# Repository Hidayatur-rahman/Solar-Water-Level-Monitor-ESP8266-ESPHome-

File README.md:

# Solar Water Level Monitor (ESP8266 + ESPHome)

A solar-powered water tank level monitoring system built around the ESP8266 (ESP-12E), designed in KiCad and running on ESPHome. It measures water level with an ultrasonic sensor, monitors battery current/voltage, and charges itself from a solar panel with a selectable-voltage MPPT charger.

## Features

- **Water level sensing** using an HC-SR04 ultrasonic distance sensor
- **Solar MPPT charging** via CN3791, with jumper-selectable input voltage (6V / 9V / 12V)
- **Battery current & voltage monitoring** using an INA219 sensor
- **1S Li-ion protection** (over-charge / over-discharge / over-current) using DW01A + FS8205A
- **5V boost converter** (MT3608) to power the ESP8266 and sensors from a single Li-ion cell
- **Deep sleep support** for low power consumption between readings
- **ESPHome integration** — no custom firmware needed, works directly with Home Assistant

## Hardware Overview

| Block | Component | Notes |
|---|---|---|
| MCU | ESP-12E (ESP8266) | Runs ESPHome |
| Water sensor | HC-SR04 | 5V supply, echo signal stepped down to 3.3V via voltage divider |
| Current/voltage sensor | INA219 | I2C, monitors battery current (charge & discharge) |
| Boost converter | MT3608 | Steps battery voltage (3.0–4.2V) up to 5V |
| Solar charger | CN3791 | MPPT buck charger, up to 4A, input jumper-selectable for 6V/9V/12V panels |
| Battery protection | DW01A + FS8205A | Standard 1S Li-ion protection circuit |
| Battery | 1x 18650 Li-ion | Not included on the board |

## Pin Connections (ESP-12E)

| Function | GPIO |
|---|---|
| I2C SDA (INA219) | GPIO4 |
| I2C SCL (INA219) | GPIO5 |
| HC-SR04 Trig | GPIO14 |
| HC-SR04 Echo (via divider) | GPIO12 |
| Deep sleep wake | GPIO16 → RST (via solder jumper) |

## Solar Panel Voltage Selection

The CN3791 MPPT tracking voltage is set by closing one solder jumper on the board.
| Panel    | Target MPPT | R18  |         |       VMPPT |
| -------- | ----------: | ---: | ------: | ----------: |
| **6 V**  |      ~5,0 V | 200k | **68k** |  **4,75 V** |
| **9 V**  |      ~8,0 V | 200k | **39k** |  **7,38 V** |
| **12 V** |     ~10,2 V | 200k | **33k** |  **8,50 V** |

> Only close **one** jumper at a time.

## Getting Started

1. Flash the board with [ESPHome](https://esphome.io/), using the provided YAML configuration (`esphome/water-level-sensor.yaml`)
2. Connect the HC-SR04, battery, and solar panel
3. Set the solar jumper according to your panel's voltage
4. Add the device to Home Assistant via the ESPHome integration

## PCB

- Designed in KiCad, 2-layer, 60x60mm
- Gerber files and schematic are in the `/hardware` folder

## License

MIT — feel free to use, modify, and build upon this project.

## Disclaimer

This is a hobbyist/DIY project. Double-check battery polarity and solar jumper settings before powering on. No warranty is provided — build and use at your own risk.

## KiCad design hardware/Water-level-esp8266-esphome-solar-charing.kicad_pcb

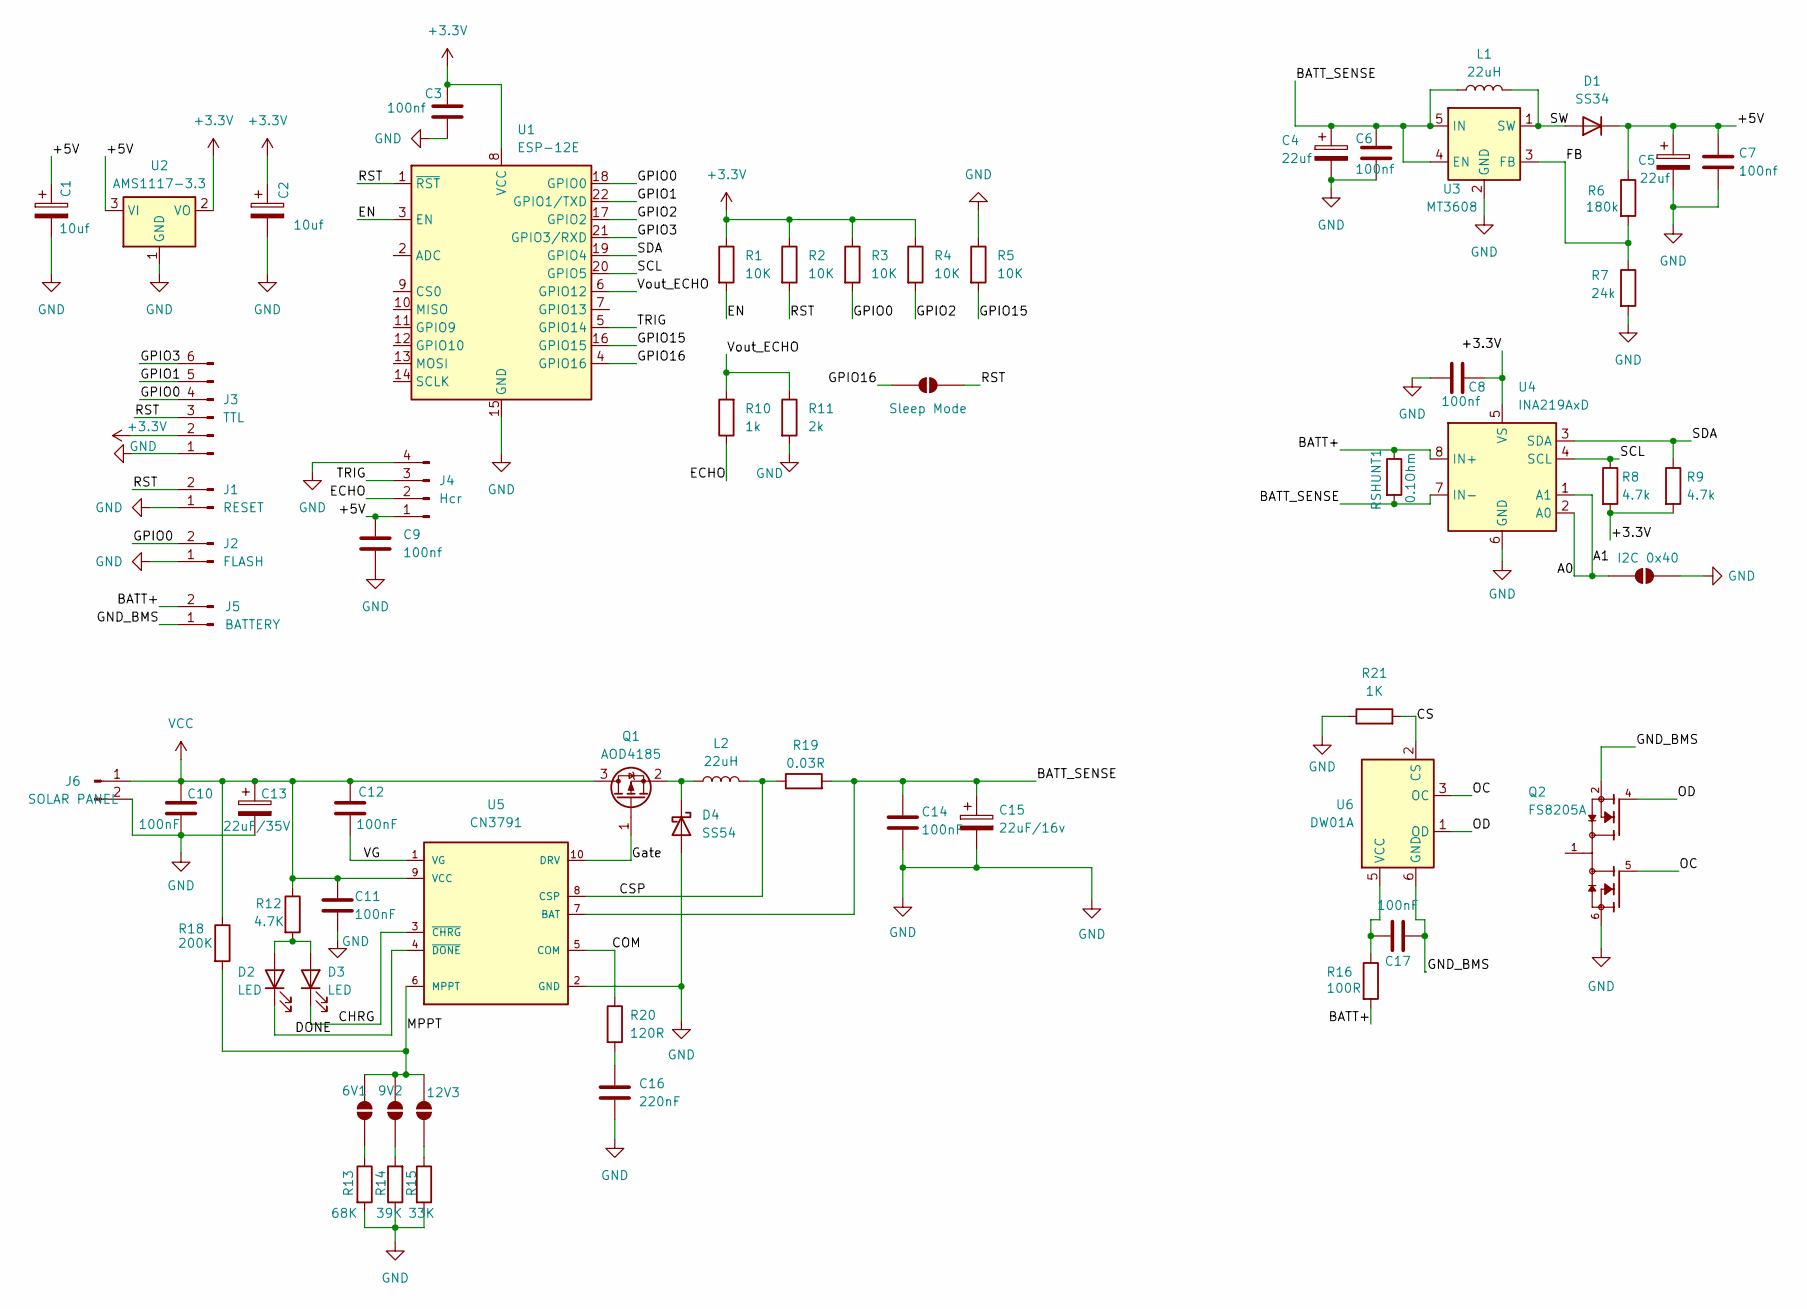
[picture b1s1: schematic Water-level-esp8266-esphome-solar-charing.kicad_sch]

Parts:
6V1, 9V2, 12V3: SolderJumper_2_Open; SolderJumper-2_P1.3mm_Open_RoundedPad1.0x1.5mm
C1, C2: 10uf; C_1206_3216Metric_Pad1.33x1.80mm_HandSolder
C3, C6, C7, C8, C9: 100nf; C_0603_1608Metric_Pad1.08x0.95mm_HandSolder
C4, C5: 22uf; C_1206_3216Metric_Pad1.33x1.80mm_HandSolder
C10, C11, C12, C14, C17: 100nF; C_0603_1608Metric_Pad1.08x0.95mm_HandSolder
C13: 22uF/35V; CP_Elec_8x6.9
C15: 22uF/16v; CP_Elec_8x6.9
C16: 220nF; C_0603_1608Metric_Pad1.08x0.95mm_HandSolder
D1: SS34; D_1206_3216Metric_Pad1.42x1.75mm_HandSolder
D2, D3: LED; LED_0805_2012Metric_Pad1.15x1.40mm_HandSolder
D4: SS54; D_SMA
J1: RESET; PinHeader_1x02_P2.54mm_Vertical
J2: FLASH; PinHeader_1x02_P2.54mm_Vertical
J3: TTL; PinHeader_1x06_P2.54mm_Vertical
J4: Hcr; PinHeader_1x04_P2.54mm_Vertical
J5: BATTERY; JST_PH_B2B-PH-K_1x02_P2.00mm_Vertical
J6: SOLAR PANEL; JST_PH_B2B-PH-K_1x02_P2.00mm_Vertical
JP1: Sleep Mode; SolderJumper-2_P1.3mm_Open_Pad1.0x1.5mm
JP2: I2C 0x40; SolderJumper-2_P1.3mm_Open_Pad1.0x1.5mm
L1: 22uH; L_Changjiang_FNR4030S
L2: 22uH; L_Changjiang_FXL1030
Q1: AOD4185; TO-252-2
Q2: FS8205A; SOP65P640X120-8N; PARTREV 1.7
R1, R2, R3, R4, R5: 10K; R_0805_2012Metric_Pad1.20x1.40mm_HandSolder
R6: 180k; R_0805_2012Metric_Pad1.20x1.40mm_HandSolder
R7: 24k; R_0805_2012Metric_Pad1.20x1.40mm_HandSolder
R8, R9: 4.7k; R_0805_2012Metric_Pad1.20x1.40mm_HandSolder
R10: 1k; R_0805_2012Metric_Pad1.20x1.40mm_HandSolder
R11: 2k; R_0805_2012Metric_Pad1.20x1.40mm_HandSolder
R12: 4.7K; R_0805_2012Metric_Pad1.20x1.40mm_HandSolder
R13: 68K; R_0805_2012Metric_Pad1.20x1.40mm_HandSolder
R14: 39K; R_0805_2012Metric_Pad1.20x1.40mm_HandSolder
R15: 33K; R_0805_2012Metric_Pad1.20x1.40mm_HandSolder
R16: 100R; R_0805_2012Metric_Pad1.20x1.40mm_HandSolder
R18: 200K; R_0805_2012Metric_Pad1.20x1.40mm_HandSolder
R19: 0.03R; R_2512_6332Metric_Pad1.40x3.35mm_HandSolder
R20: 120R; R_0805_2012Metric_Pad1.20x1.40mm_HandSolder
R21: 1K; R_0805_2012Metric_Pad1.20x1.40mm_HandSolder
RSHUNT1: 0.1Ohm; R_2512_6332Metric_Pad1.40x3.35mm_HandSolder
U1: ESP-12E
U2: AMS1117-3.3; SOT-223-3_TabPin2
U3: MT3608; SOT-23-6
U4: INA219AxD; SOIC-8_3.9x4.9mm_P1.27mm
U5: CN3791; CN3791_SSOP10
U6: DW01A; SOT-23-6

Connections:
+3.3V: C2.1, C3.1, C8.2, J3.2, R1.1, R2.1, R3.1, R4.1, R8.2, R9.2, U1.8 (VCC), U2.2 (VO), U4.5 (VS)
/+5V: C1.1, C5.1, C7.1, C9.1, D1.1 (K), J4.1, R6.1, U2.3 (VI)
/A0: JP2.2 (B), U4.1 (A1), U4.2 (A0)
/BATT+: J5.2, R16.2, RSHUNT1.1, U4.8 (IN+)
/BATT_SENSE: C4.1, C6.1, C14.1, C15.1, L1.1, R19.2, RSHUNT1.2, U3.4 (EN), U3.5 (IN), U4.7 (IN-), U5.7 (BAT)
/CHRG: D3.1 (K), U5.3 (~CHRG)
/COM: R20.1, U5.5 (COM)
/CS: R21.2, U6.2 (CS)
/CSP: L2.2, R19.1, U5.8 (CSP)
/DONE: D2.1 (K), U5.4 (~DONE)
/ECHO: J4.2, R10.1
/EN: R1.2, U1.3 (EN)
/FB: R6.2, R7.1, U3.3 (FB)
/GND_BMS: C17.2, J5.1, Q2.2, Q2.3, U6.6 (GND)
/GPIO0: J2.2, J3.4, R3.2, U1.18 (GPIO0)
/GPIO1: J3.5, U1.22 (GPIO1/TXD)
/GPIO2: R4.2, U1.17 (GPIO2)
/GPIO3: J3.6, U1.21 (GPIO3/RXD)
/GPIO15: R5.2, U1.16 (GPIO15)
/GPIO16: JP1.2 (B), U1.4 (GPIO16)
/Gate: Q1.1 (G), U5.10 (DRV)
/MPPT: 6V1.2 (B), 9V2.1 (A), 12V3.2 (B), R18.2, U5.6 (MPPT)
/OC: Q2.5, U6.3 (OC)
/OD: Q2.4, U6.1 (OD)
/RST: J1.2, J3.3, JP1.1 (A), R2.2, U1.1 (~RST)
/SCL: R8.1, U1.20 (GPIO5), U4.4 (SCL)
/SDA: R9.1, U1.19 (GPIO4), U4.3 (SDA)
/SW: D1.2 (A), L1.2, U3.1 (SW)
/TRIG: J4.3, U1.5 (GPIO14)
/VG: C12.2, U5.1 (VG)
/Vout_ECHO: R10.2, R11.1, U1.6 (GPIO12)
GND: C1.2, C2.2, C3.2, C4.2, C5.2, C6.2, C7.2, C8.1, C9.2, C10.2, C11.2, C13.2, C14.2, C15.2, C16.2, D4.2 (A), J1.1, J2.1, J3.1, J4.4, J6.2, JP2.1 (A), Q2.6, Q2.7, R5.1, R7.2, R11.2, R13.2, R14.1, R15.2, R21.1, U1.15 (GND), U2.1 (GND), U3.2 (GND), U4.6 (GND), U5.2 (GND)
unnamed: 6V1.1 (A), R13.1
unnamed: 9V2.2 (B), R14.2
unnamed: 12V3.1 (A), R15.1
unnamed: C16.1, R20.2
unnamed: D2.2 (A), D3.2 (A), R12.2
unnamed: D4.1 (K), L2.1, Q1.2 (S)
unnamed: Q2.1, Q2.8
unnamed: C17.1, R16.1, U6.5 (VCC)
VCC: C10.1, C11.1, C12.1, C13.1, J6.1, Q1.3 (D), R12.1, R18.1, U5.9 (VCC)

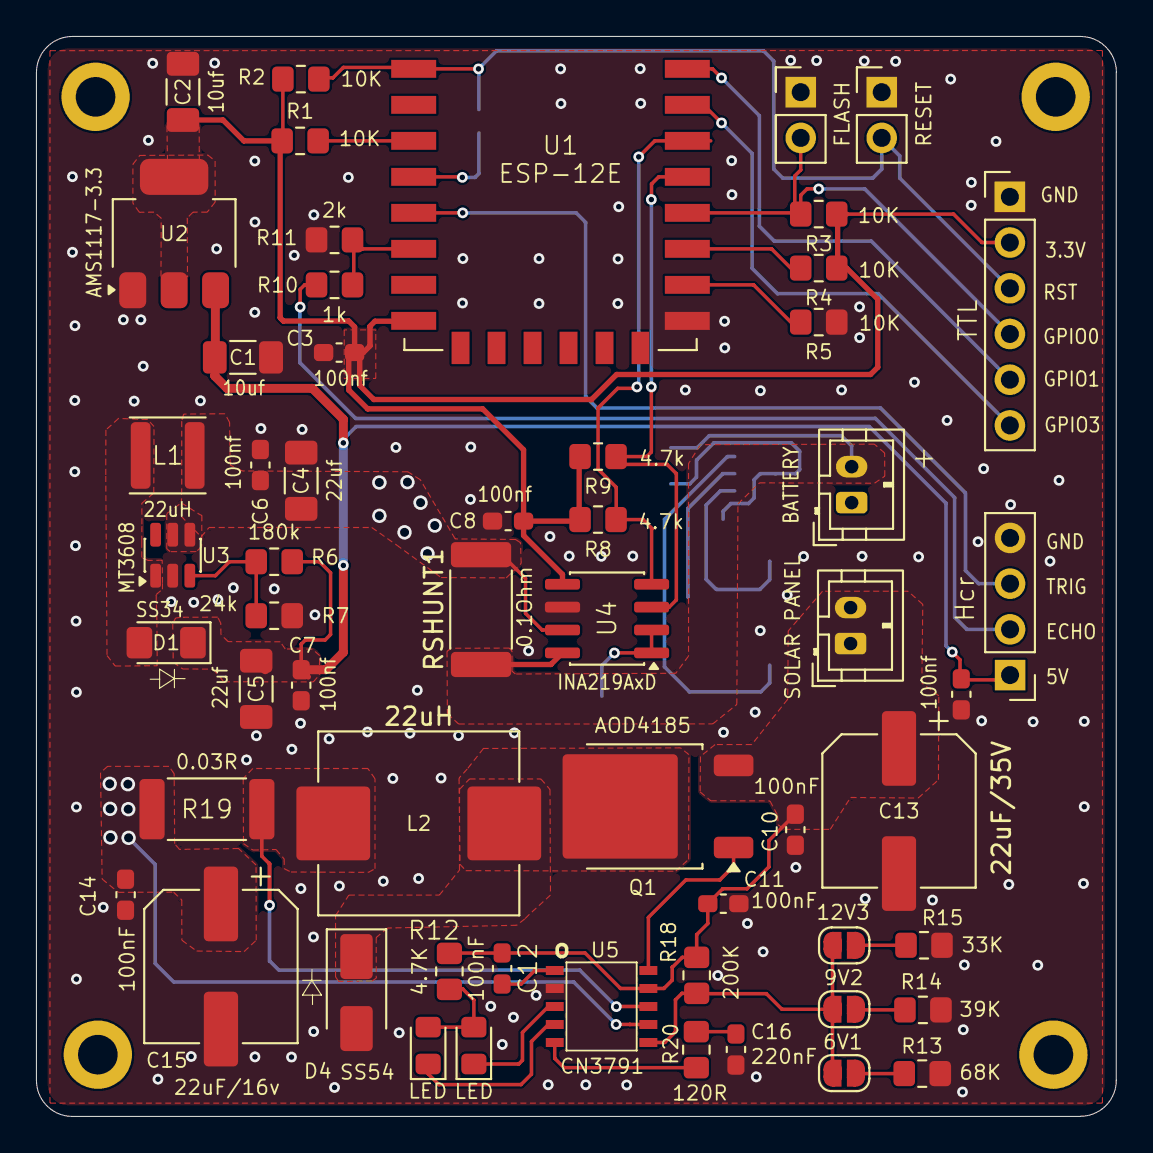
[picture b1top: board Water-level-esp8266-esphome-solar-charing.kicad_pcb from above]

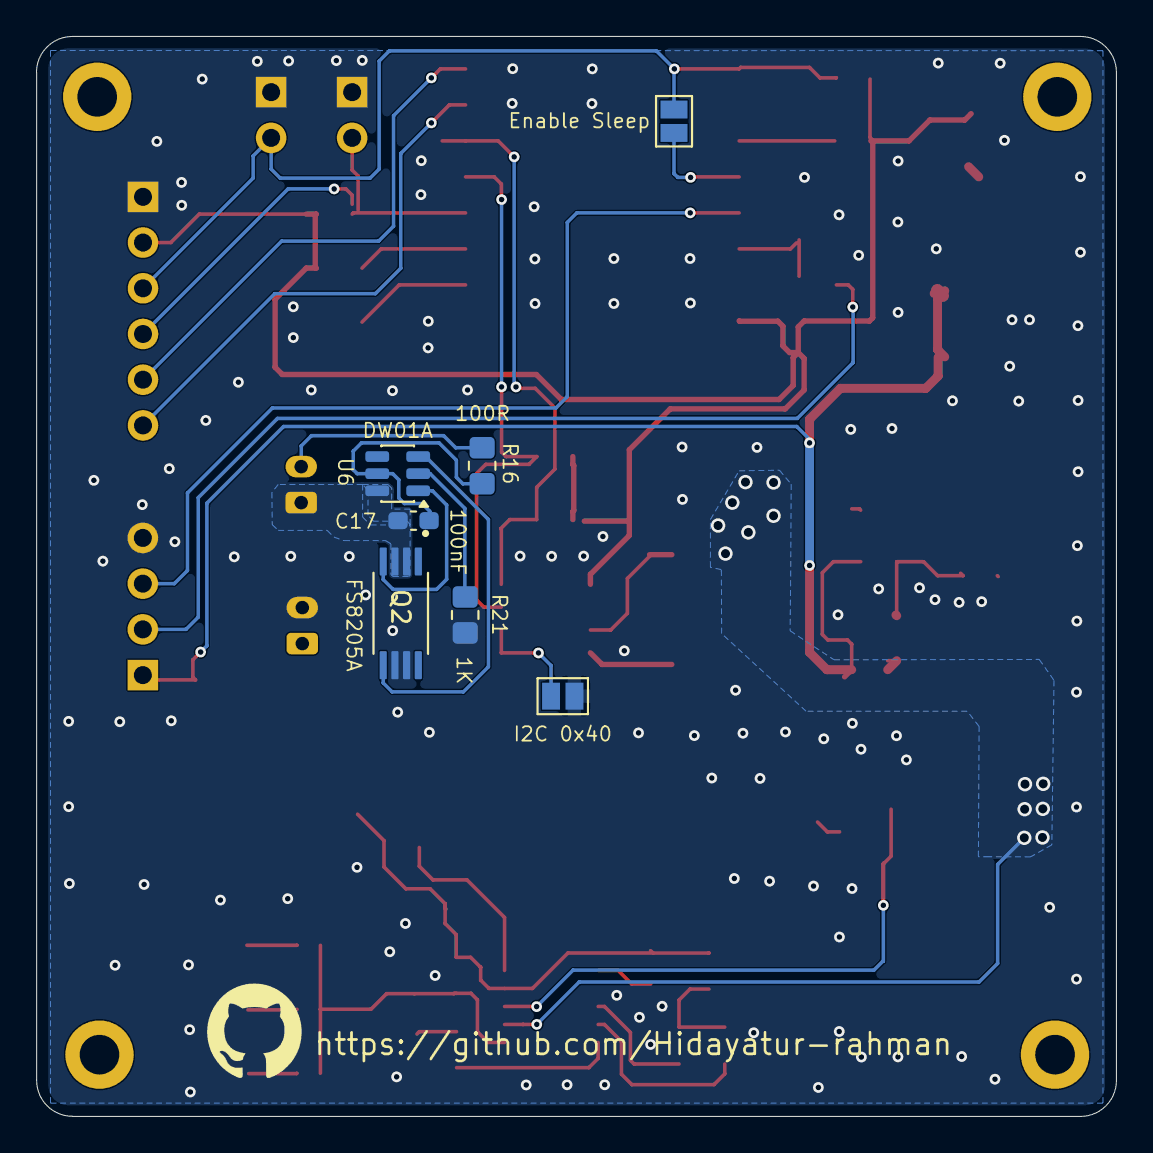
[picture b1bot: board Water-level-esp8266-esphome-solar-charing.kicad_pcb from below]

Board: 2 copper layers, 60.0 x 60.0 mm, 63 parts (7 on the bottom side), 41 nets.

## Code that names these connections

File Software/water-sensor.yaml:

esphome:
  name: water-sensor-tandon
  friendly_name: Water Sensor Tandon

esp8266:
  board: nodemcuv2

# Enable logging
logger:
  level: DEBUG

# Enable Home Assistant API
api:
  # encryption:
  #   key: "00000"

ota:
  platform: esphome

wifi:
  ssid: !secret wifi_ssid
  password: !secret wifi_password
  min_auth_mode: WPA2
  fast_connect: true
  power_save_mode: none
  reboot_timeout: 5min

  on_connect:
    - light.turn_on: wifi_led

  on_disconnect:
    - light.turn_off: wifi_led

deep_sleep:
  id: deep_sleep_control

time:
  - platform: sntp
    id: waktu_sistem
    timezone: Asia/Makassar

output:
  - platform: gpio
    pin:
      number: GPIO2
      inverted: true
    id: led_wifi_output

light:
  - platform: binary
    name: "LED WiFi"
    output: led_wifi_output
    id: wifi_led


# =========================
# GLOBAL VARIABLE
# =========================
globals:

  - id: baterai_lemah_v
    type: float
    restore_value: no
    initial_value: '3.00'

i2c:
  sda: GPIO4
  scl: GPIO5
  scan: true

binary_sensor:
  - platform: homeassistant
    name: "Status Mesin Air"
    id: mesin_air_ha
    entity_id: switch.mesin_air_water_pump_relay_2

# === SENSOR ===
sensor:
  # ---- INA219 Battery Monitoring ----
  - platform: ina219
    address: 0x40
    shunt_resistance: 0.1 ohm
    update_interval: 10s

    current:
      name: "Arus Baterai Kost"
      id: arus_baterai_kost
      unit_of_measurement: "A"
      accuracy_decimals: 3
      filters:
        - median:
            window_size: 5
            send_every: 3
        - exponential_moving_average:
            alpha: 0.2

    bus_voltage:
      name: "Tegangan Baterai Kost"
      id: tegangan_baterai_kost
      unit_of_measurement: "V"
      accuracy_decimals: 2
      filters:
        - median:
            window_size: 5
            send_every: 3
        - exponential_moving_average:
            alpha: 0.2

    power:
      name: "Daya Kost"
      unit_of_measurement: "W"
      accuracy_decimals: 2
      filters:
        - median:
            window_size: 5
            send_every: 3
        - exponential_moving_average:
            alpha: 0.2

# ---- Ultrasonic Water Level (D5=GPIO14 trigger, D6=GPIO12 echo) ----
  - platform: ultrasonic
    trigger_pin: GPIO14
    echo_pin: GPIO12
    name: "Water Level Kost"
    id: persen_air
    update_interval: 10s
    unit_of_measurement: "%"
    accuracy_decimals: 1
    filters:
      - filter_out: nan
      - median:
          window_size: 5
          send_every: 3
          send_first_at: 3
      - exponential_moving_average:
          alpha: 0.2
          send_every: 1
      - lambda: |-
          const float low_level = 1.30;   // permukaan air saat kosong
          const float high_level = 0.30;  // permukaan air saat penuh

          if (x > low_level) {
            return 0.0;
          } else if (x < high_level) {
            return 100.0;
          } else {
            return (1.0 - (x - high_level) / (low_level - high_level)) * 100.0;
          }


  # ---- Persentase Baterai dari bus_voltage INA219 ----
  - platform: template
    name: "Persentase Baterai Kost"
    id: persentase_baterai_kost
    unit_of_measurement: "%"
    accuracy_decimals: 0
    update_interval: 10s
    lambda: |-
      if (!id(tegangan_baterai_kost).has_state() || isnan(id(tegangan_baterai_kost).state)) return {};
      float voltage = id(tegangan_baterai_kost).state;
      float min_v = id(baterai_lemah_v);
      float max_v = 4.2;   // baterai penuh
      float pct = ((voltage - min_v) / (max_v - min_v)) * 100.0;
      if (pct > 100) pct = 100;
      if (pct < 0) pct = 0;
      return pct;
    filters:
      - median:
          window_size: 5
          send_every: 3
          send_first_at: 3
      - exponential_moving_average:
          alpha: 0.2
          send_every: 1

# =========================
# LOGIKA DEEP SLEEP ADAPTIF
# Prioritas pengecekan (dari atas ke bawah):
#   1. Mesin air MENYALA         -> TIDAK PERNAH sleep, apapun kondisi lain
#   2. Baterai lemah             -> sleep panjang (2 jam), selamatkan baterai
#   3. Malam + air >=80%         -> sleep 1 jam
#   4. Malam + air <80%          -> TIDAK sleep (HA masih isi air, tunggu sampai penuh)
#   5. Siang                     -> TIDAK PERNAH sleep, apapun level airnya
#
# "Siang" = 06:00-19:59, "Malam" = 20:00-05:59.
# ESP tetap aktif 10 menit tiap siklus (jendela OTA) sebelum evaluasi --
# ini sekaligus cukup untuk NTP sync (biasanya cuma 2-5 detik), jadi
# tidak perlu pengecekan sync terpisah lagi.
# =========================
interval:
  - interval: 10min
    then:
      # ESP tetap AWAKE selama 10 menit penuh setelah bangun/boot --
      # cukup untuk sempat push OTA kalau perlu, dan supaya semua sensor
      # (terutama yang pakai filter median/EMA) sempat stabil sebelum
      # dipakai untuk pengambilan keputusan di bawah.
      - logger.log: "ESP aktif 5 menit, silakan upload OTA sekarang kalau perlu."
      - delay: 5min

      - lambda: |-
          if (id(persen_air).has_state()) {
            ESP_LOGI("main", "Persentase air: %.1f%%", id(persen_air).state);
          }
          if (id(tegangan_baterai_kost).has_state()) {
            ESP_LOGI("main", "Tegangan baterai: %.2fV", id(tegangan_baterai_kost).state);
          }
          if (id(mesin_air_ha).has_state()) {
            ESP_LOGI("main", "Status mesin air: %s", id(mesin_air_ha).state ? "ON" : "OFF");
          } else {
            ESP_LOGW("main", "Status mesin air belum tersedia / belum terbaca");
          }
          auto t = id(waktu_sistem).now();
          if (t.is_valid()) {
            ESP_LOGI("main", "Jam sekarang: %02d:%02d", t.hour, t.minute);
          } else {
            ESP_LOGW("main", "Waktu belum sinkron (NTP belum berhasil)");
          }

      # ---- 1. Mesin air menyala -> prioritas tertinggi, jangan sleep ----
      - if:
          condition:
            lambda: |-
              return id(mesin_air_ha).has_state() && id(mesin_air_ha).state;

          then:
            - logger.log: "Mesin air menyala, ESP TIDAK sleep."

          else:
            # ---- 2. Baterai lemah -> sleep panjang, selamatkan baterai ----
            - if:
                condition:
                  lambda: |-
                    return id(tegangan_baterai_kost).has_state()
                        && id(tegangan_baterai_kost).state < id(baterai_lemah_v);

                then:
                  - logger.log: "Baterai lemah, sleep 2 jam untuk menghemat baterai."
                  - deep_sleep.enter:
                      id: deep_sleep_control
                      sleep_duration: 2h

                else:
                  # ---- 3. Hanya sleep di MALAM hari, dan hanya kalau air sudah >=70% ----
                  # Siang hari: TIDAK PERNAH sleep, apapun level airnya.
                  - if:
                      # true = malam (20:00-05:59), false = siang (06:00-19:59).
                      # Kalau waktu belum sinkron, anggap SIANG (safe default)
                      # supaya device tetap cek lebih sering, bukan sleep buta.
                      condition:
                        lambda: |-
                          auto t = id(waktu_sistem).now();
                          if (!t.is_valid()) {
                            return false;  // anggap siang
                          }
                          return t.hour >= 20 || t.hour < 6;

                      then:
                        # ---- MALAM ----
                        - if:
                            condition:
                              lambda: |-
                                return id(persen_air).has_state()
                                    && id(persen_air).state >= 70.0;

                            then:
                              - logger.log: "Malam, air >=70%, sleep 1 jam."
                              - deep_sleep.enter:
                                  id: deep_sleep_control
                                  sleep_duration: 1h

                            else:
                              - logger.log: "Malam, air <70% (menunggu HA isi air), ESP TIDAK sleep."

                      else:
                        # ---- SIANG ----
                        - logger.log: "Siang hari, ESP TIDAK sleep."

# === SWITCH ===
switch:
  - platform: restart
    name: "Restart Sensor Water Level"

# === STATUS CHARGING / DISCHARGING ===
# text_sensor:
#   - platform: template
#     name: "Status Baterai"
#     id: battery_status
#     icon: "mdi:battery-charging"
#     lambda: |-
#       if (id(arus_baterai_kost).state > 0.02) {
#         return std::string("🔆 Charging");
#       } else if (id(arus_baterai_kost).state < -0.02) {
#         return std::string("🪫 Discharging");
#       } else {
#         return std::string("⚡ Standby");
#       }
